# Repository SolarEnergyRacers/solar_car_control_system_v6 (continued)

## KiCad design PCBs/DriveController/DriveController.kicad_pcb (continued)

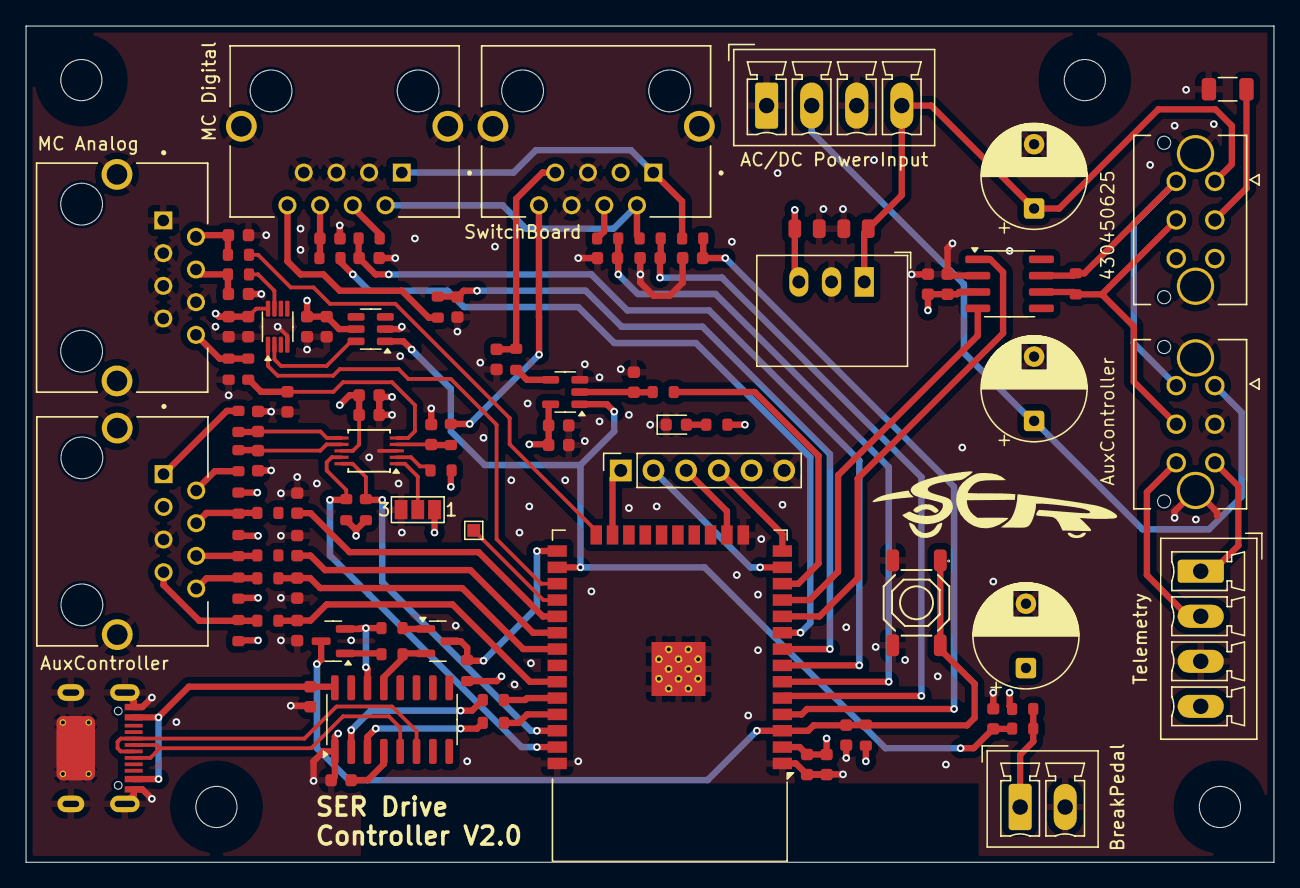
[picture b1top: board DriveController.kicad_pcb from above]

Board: 4 copper layers, 97.0 x 65.0 mm, 106 parts (0 on the bottom side), 75 nets.

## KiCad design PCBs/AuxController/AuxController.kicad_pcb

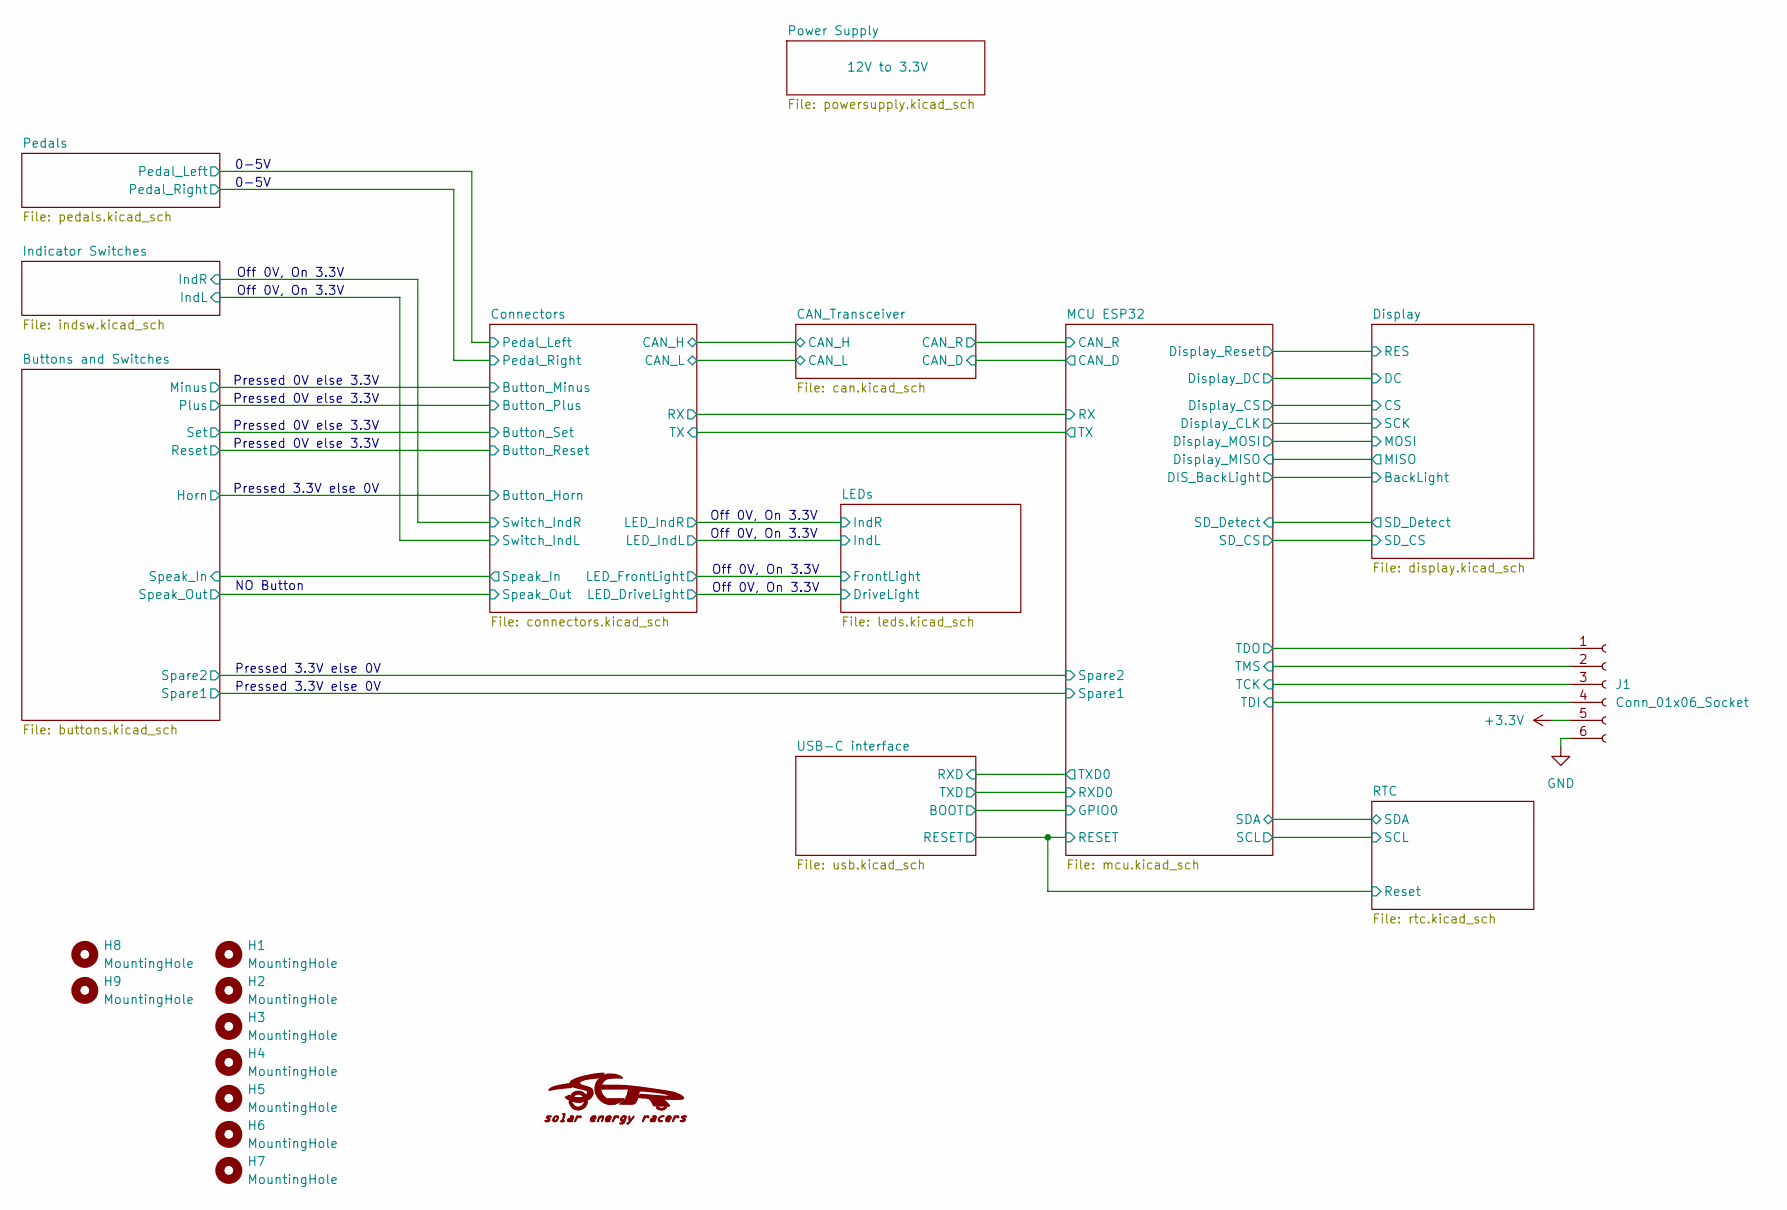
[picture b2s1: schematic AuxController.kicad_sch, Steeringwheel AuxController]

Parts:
G1: LOGO; SER_Logo
H1, H2, H3, H4, H5, H6, H7: MountingHole; MountingHole_3.2mm_M3_No_Copper
H8, H9: MountingHole; MountingHole_6.5mm_mod
J1: Conn_01x06_Socket; PinSocket_1x06_P2.54mm_Horizontal

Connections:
+3.3V: J1.5; also elsewhere on the board
/MCU ESP32/TCK: J1.3; also elsewhere on the board
/MCU ESP32/TDI: J1.4; also elsewhere on the board
/MCU ESP32/TDO: J1.1; also elsewhere on the board
/MCU ESP32/TMS: J1.2; also elsewhere on the board
GND: J1.6; also elsewhere on the board

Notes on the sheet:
Pressed 0V else 3.3V
0-5V
NO Button
Off 0V, On 3.3V
Pressed 3.3V else 0V

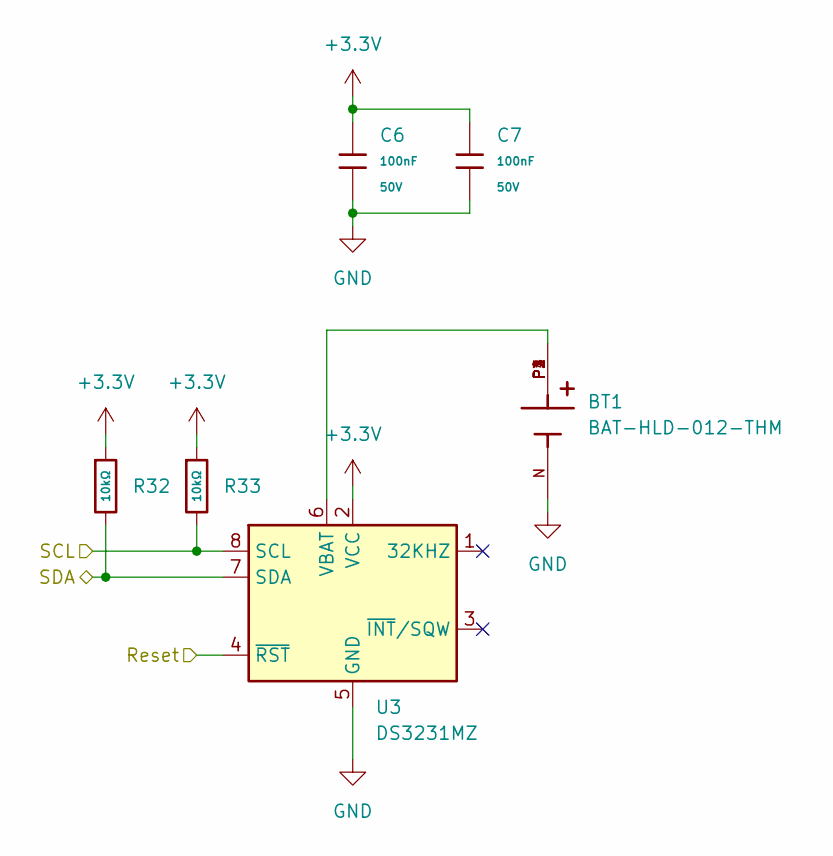
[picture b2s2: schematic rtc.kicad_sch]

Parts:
BT1: BAT-HLD-012-THM; BAT_BAT-HLD-012-THM
C6, C7: 100nF; C_0603; Voltage Rated 50V; Tolerance ±10%; Part CC0603KRX7R9BB104; LCSC C14663
R32, R33: 10kΩ; R_0603; Overload Voltage (Max) 75V; Tolerance ±1%; Part 0603WAF1002T5E; LCSC C25804
U3: DS3231MZ; SOIC-8_3.9x4.9mm_P1.27mm

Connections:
+3.3V: C6.1, C7.1, R32.1, R33.1, U3.2 (VCC); also elsewhere on the board
/MCU ESP32/RESET: U3.4 (~RST); also elsewhere on the board
/MCU ESP32/SCL: R33.2, U3.8 (SCL); also elsewhere on the board
/MCU ESP32/SDA: R32.2, U3.7 (SDA); also elsewhere on the board
GND: BT1.N, C6.2, C7.2, U3.5 (GND); also elsewhere on the board
unnamed: BT1.P1, BT1.P2, BT1.P3, BT1.P4, U3.6 (VBAT)

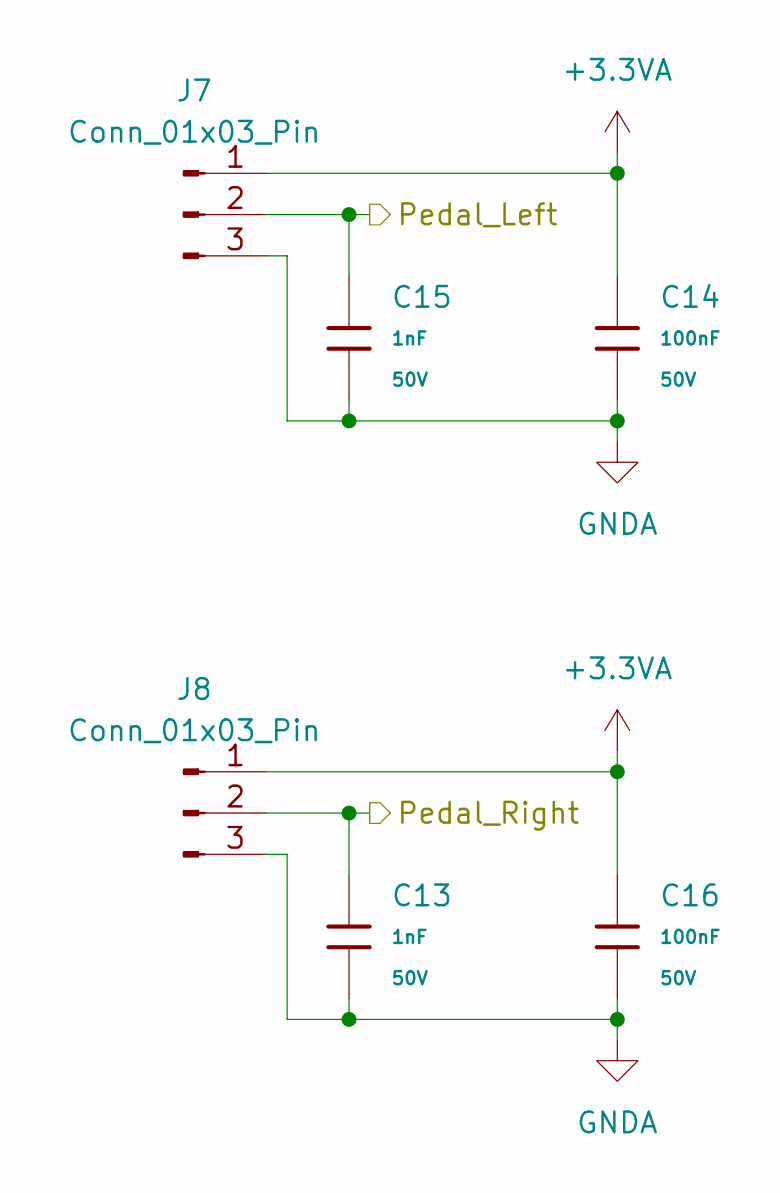
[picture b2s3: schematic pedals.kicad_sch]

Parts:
C13, C15: 1nF; C_0603; Voltage Rated 50V; Tolerance ±10%; Part CL10B102KB8NNNC; LCSC C1588
C14, C16: 100nF; C_0603; Voltage Rated 50V; Tolerance ±10%; Part CC0603KRX7R9BB104; LCSC C14663
J7, J8: Conn_01x03_Pin; PinHeader_1x03_P2.54mm_Vertical

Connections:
+3.3VA: C14.1, C16.1, J7.1, J8.1; also elsewhere on the board
/Connectors/Pedal_Left: C15.1, J7.2; also elsewhere on the board
/Connectors/Pedal_Right: C13.1, J8.2; also elsewhere on the board
GNDA: C13.2, C14.2, C15.2, C16.2, J7.3, J8.3; also elsewhere on the board

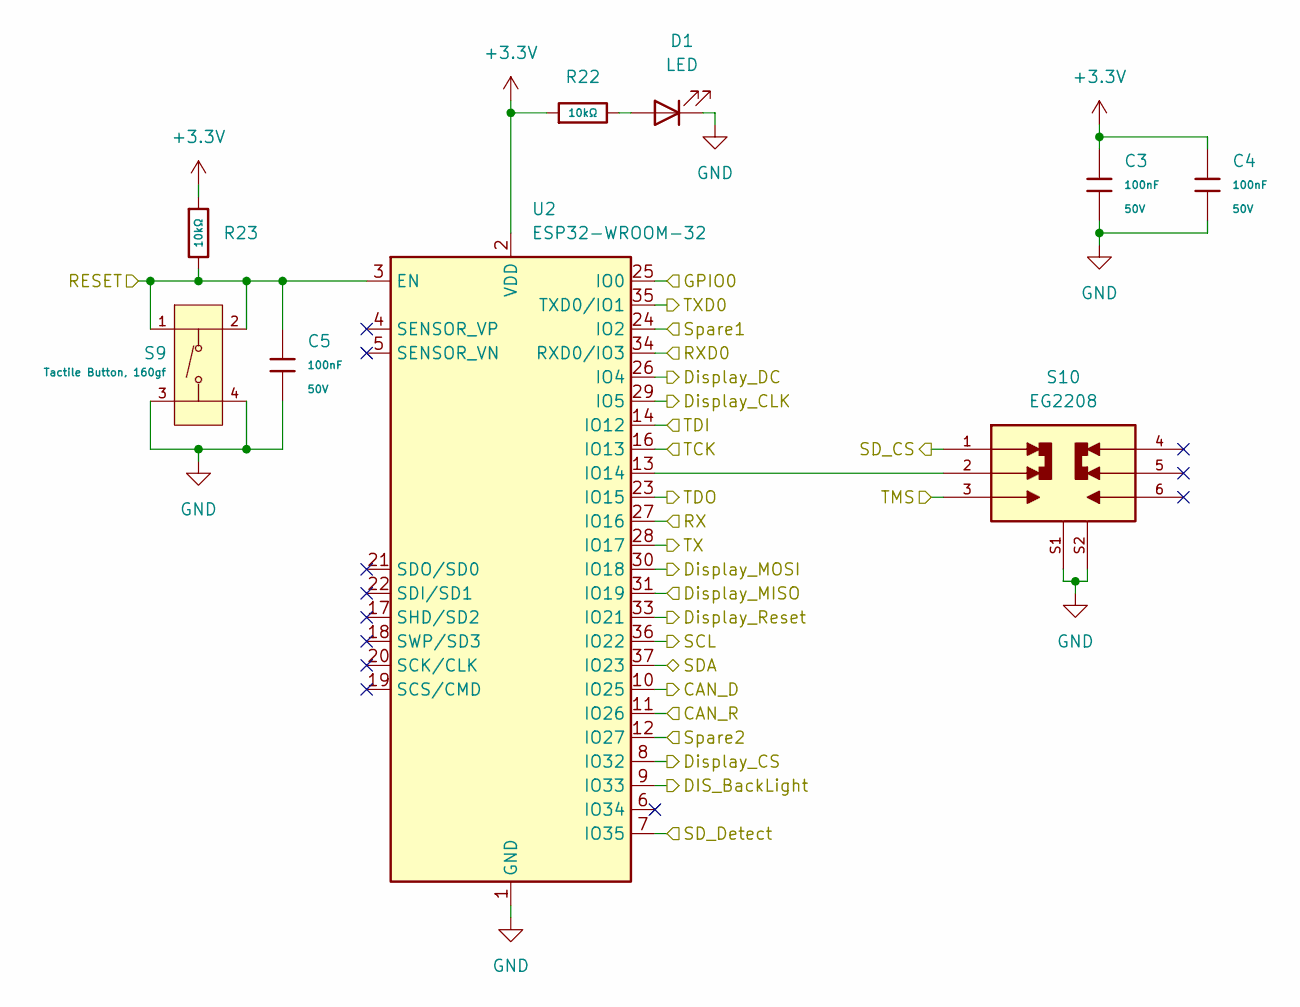
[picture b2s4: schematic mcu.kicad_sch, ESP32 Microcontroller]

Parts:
C3, C4, C5: 100nF; C_0603; Voltage Rated 50V; Tolerance ±10%; Part CC0603KRX7R9BB104; LCSC C14663
D1: LED; LED_0603_1608Metric
R22, R23: 10kΩ; R_0603; Overload Voltage (Max) 75V; Tolerance ±1%; Part 0603WAF1002T5E; LCSC C25804
S9: Tactile Button, 160gf; SW-SMD_4P-L5.1-W5.1-P3.70-LS6.5-TL-2; Voltage Rating (Dc) 12V; Part TS-1187A-B-A-B; LCSC C318884
S10: EG2208; SW_EG2208; PARTREV C
U2: ESP32-WROOM-32

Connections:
+3.3V: C3.1, C4.1, R22.1, R23.1, U2.2 (VDD); also elsewhere on the board
/Buttons and Switches/Spare1: U2.24 (IO2); also elsewhere on the board
/Buttons and Switches/Spare2: U2.12 (IO27); also elsewhere on the board
/CAN_Transceiver/CAN_D: U2.10 (IO25); also elsewhere on the board
/CAN_Transceiver/CAN_R: U2.11 (IO26); also elsewhere on the board
/Connectors/RX: U2.27 (IO16); also elsewhere on the board
/Connectors/TX: U2.28 (IO17); also elsewhere on the board
/Display/BackLight: U2.9 (IO33); also elsewhere on the board
/Display/CS: U2.8 (IO32); also elsewhere on the board
/Display/DC: U2.26 (IO4); also elsewhere on the board
/Display/MISO: U2.31 (IO19); also elsewhere on the board
/Display/MOSI: U2.30 (IO18); also elsewhere on the board
/Display/RES: U2.33 (IO21); also elsewhere on the board
/Display/SCK: U2.29 (IO5); also elsewhere on the board
/Display/SD_CS: S10.1; also elsewhere on the board
/Display/SD_Detect: U2.7 (IO35); also elsewhere on the board
/MCU ESP32/GPIO0: U2.25 (IO0); also elsewhere on the board
/MCU ESP32/RESET: C5.1, R23.2, S9.1 (A), S9.2 (B), U2.3 (EN); also elsewhere on the board
/MCU ESP32/RXD0: U2.34 (RXD0/IO3); also elsewhere on the board
/MCU ESP32/SCL: U2.36 (IO22); also elsewhere on the board
/MCU ESP32/SDA: U2.37 (IO23); also elsewhere on the board
/MCU ESP32/TCK: U2.16 (IO13); also elsewhere on the board
/MCU ESP32/TDI: U2.14 (IO12); also elsewhere on the board
/MCU ESP32/TDO: U2.23 (IO15); also elsewhere on the board
/MCU ESP32/TMS: S10.3; also elsewhere on the board
/MCU ESP32/TXD0: U2.35 (TXD0/IO1); also elsewhere on the board
GND: C3.2, C4.2, C5.2, D1.1 (K), S9.3 (C), S9.4 (D), S10.S1, S10.S2, U2.1 (GND), U2.15 (GND), U2.38 (GND), U2.39 (GND); also elsewhere on the board
unnamed: D1.2 (A), R22.2
unnamed: S10.2, U2.13 (IO14)

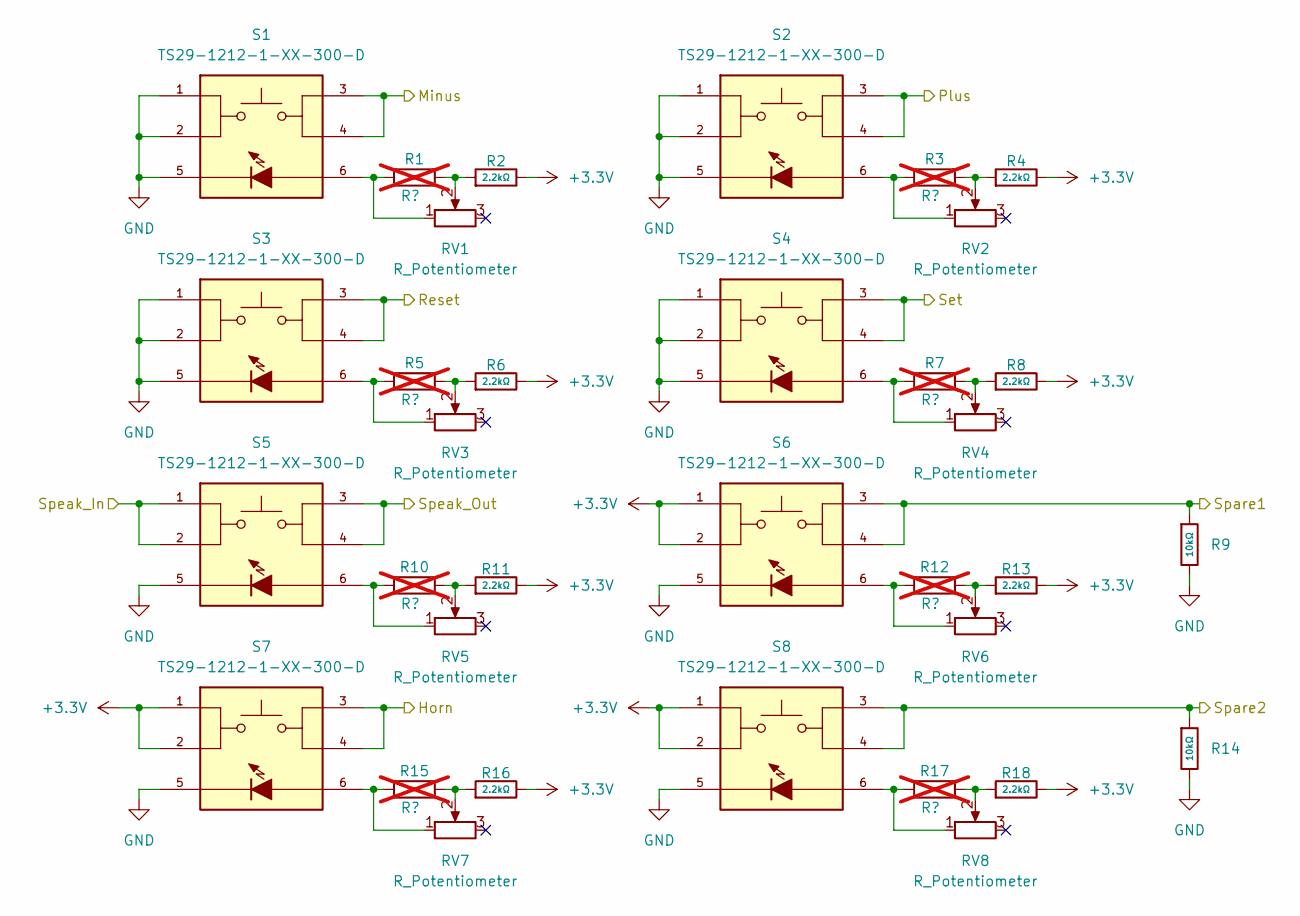
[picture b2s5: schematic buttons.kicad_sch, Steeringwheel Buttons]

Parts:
R1, R3, R5, R7, R10, R12, R15, R17: R?; R_0603_1608Metric; not fitted
R2, R4, R6, R8, R11, R13, R16, R18: 2.2kΩ; R_0603; Overload Voltage (Max) 75V; Tolerance ±1%; Part 0603WAF2201T5E; LCSC C4190
R9, R14: 10kΩ; R_0603; Overload Voltage (Max) 75V; Tolerance ±1%; Part 0603WAF1002T5E; LCSC C25804
RV1, RV2, RV3, RV4, RV5, RV6, RV7, RV8: R_Potentiometer; Potentiometer_Bourns_TC33X_Vertical
S1, S2, S3, S4, S5, S6, S7, S8: TS29-1212-1-XX-300-D; SW_TS29-1212-1-XX-300-D_mod; PARTREV 1.01

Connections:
+3.3V: R2.2, R4.2, R6.2, R8.2, R11.2, R13.2, R16.2, R18.2, S6.1, S6.2, S7.1, S7.2, S8.1, S8.2; also elsewhere on the board
/Buttons and Switches/Horn: S7.3, S7.4; also elsewhere on the board
/Buttons and Switches/Minus: S1.3, S1.4; also elsewhere on the board
/Buttons and Switches/Plus: S2.3, S2.4; also elsewhere on the board
/Buttons and Switches/Reset: S3.3, S3.4; also elsewhere on the board
/Buttons and Switches/Set: S4.3, S4.4; also elsewhere on the board
/Buttons and Switches/Spare1: R9.1, S6.3, S6.4; also elsewhere on the board
/Buttons and Switches/Spare2: R14.1, S8.3, S8.4; also elsewhere on the board
/Buttons and Switches/Speak_In: S5.1, S5.2; also elsewhere on the board
/Buttons and Switches/Speak_Out: S5.3, S5.4; also elsewhere on the board
GND: R9.2, R14.2, S1.1, S1.2, S1.5, S2.1, S2.2, S2.5, S3.1, S3.2, S3.5, S4.1, S4.2, S4.5, S5.5, S6.5, S7.5, S8.5; also elsewhere on the board
unnamed: R1.1, RV1.1, S1.6
unnamed: R1.2, R2.1, RV1.2
unnamed: R3.1, RV2.1, S2.6
unnamed: R3.2, R4.1, RV2.2
unnamed: R5.1, RV3.1, S3.6
unnamed: R5.2, R6.1, RV3.2
unnamed: R7.1, RV4.1, S4.6
unnamed: R7.2, R8.1, RV4.2
unnamed: R10.1, RV5.1, S5.6
unnamed: R10.2, R11.1, RV5.2
unnamed: R12.1, RV6.1, S6.6
unnamed: R12.2, R13.1, RV6.2
unnamed: R15.1, RV7.1, S7.6
unnamed: R15.2, R16.1, RV7.2
unnamed: R17.1, RV8.1, S8.6
unnamed: R17.2, R18.1, RV8.2

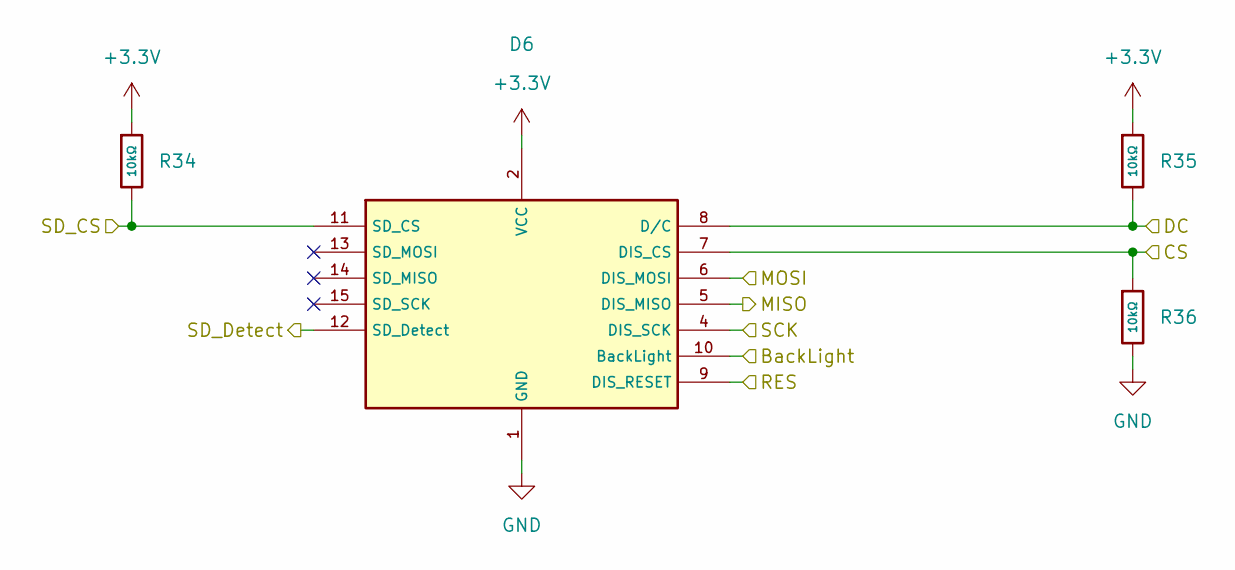
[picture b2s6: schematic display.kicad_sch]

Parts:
D6: ILI93_Display_Adafruit
R34, R35, R36: 10kΩ; R_0603; Overload Voltage (Max) 75V; Tolerance ±1%; Part 0603WAF1002T5E; LCSC C25804

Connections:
+3.3V: D6.2 (VCC), R34.1, R35.1; also elsewhere on the board
/Display/BackLight: D6.10 (BackLight); also elsewhere on the board
/Display/CS: D6.7 (DIS_CS), R36.1; also elsewhere on the board
/Display/DC: D6.8 (D/C), R35.2; also elsewhere on the board
/Display/MISO: D6.5 (DIS_MISO); also elsewhere on the board
/Display/MOSI: D6.6 (DIS_MOSI); also elsewhere on the board
/Display/RES: D6.9 (DIS_RESET); also elsewhere on the board
/Display/SCK: D6.4 (DIS_SCK); also elsewhere on the board
/Display/SD_CS: D6.11 (SD_CS), R34.2; also elsewhere on the board
/Display/SD_Detect: D6.12 (SD_Detect); also elsewhere on the board
GND: D6.1 (GND), R36.2; also elsewhere on the board

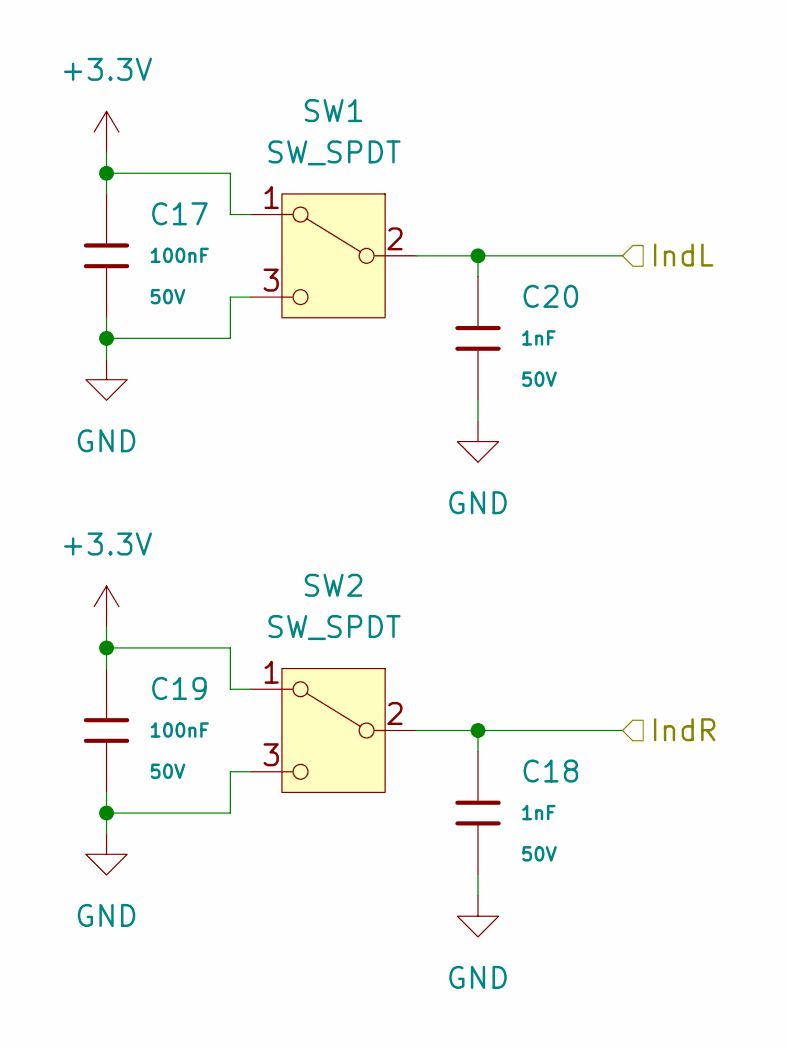
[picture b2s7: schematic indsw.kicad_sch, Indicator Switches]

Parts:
C17, C19: 100nF; C_0603; Voltage Rated 50V; Tolerance ±10%; Part CC0603KRX7R9BB104; LCSC C14663
C18, C20: 1nF; C_0603; Voltage Rated 50V; Tolerance ±10%; Part CL10B102KB8NNNC; LCSC C1588
SW1, SW2: SW_SPDT; PinHeader_1x03_P2.54mm_Vertical

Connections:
+3.3V: C17.1, C19.1, SW1.1 (A), SW2.1 (A); also elsewhere on the board
/Connectors/Switch_IndL: C20.1, SW1.2 (B); also elsewhere on the board
/Connectors/Switch_IndR: C18.1, SW2.2 (B); also elsewhere on the board
GND: C17.2, C18.2, C19.2, C20.2, SW1.3 (C), SW2.3 (C); also elsewhere on the board

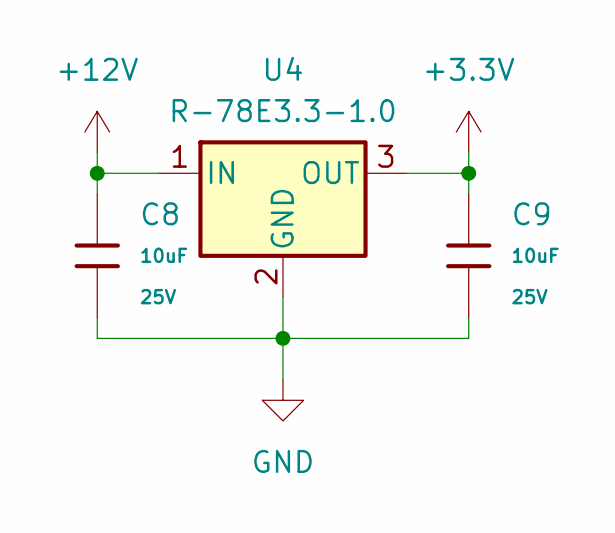
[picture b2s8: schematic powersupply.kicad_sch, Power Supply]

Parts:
C8, C9: 10uF; C_0805; Voltage Rated 25V; Tolerance ±10%; Part CL21A106KAYNNNE; LCSC C15850
U4: R-78E3.3-1.0; Converter_DCDC_RECOM_R-78E-0.5_THT

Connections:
+3.3V: C9.1, U4.3 (OUT); also elsewhere on the board
+12V: C8.1, U4.1 (IN); also elsewhere on the board
GND: C8.2, C9.2, U4.2 (GND); also elsewhere on the board

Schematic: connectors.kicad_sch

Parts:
J2: DriveController; CUI_CRJ027-1-TH; PARTREV 1.0
J3: 430450625; MOLEX_430450625; PARTREV H4
J4: Radio Enable; SAMESKY_SJ1-2503A; PARTREV 1.06
J5: ChassisBoard; CUI_CRJ027-1-TH; PARTREV 1.0
R19, R20, R42: R; R_0603_1608Metric; not fitted

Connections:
+3.3VA: J2.3; also elsewhere on the board
+12V: J3.1; also elsewhere on the board
/Buttons and Switches/Horn: J5.5; also elsewhere on the board
/Buttons and Switches/Minus: J2.8; also elsewhere on the board
/Buttons and Switches/Plus: J2.6; also elsewhere on the board
/Buttons and Switches/Reset: J2.7; also elsewhere on the board
/Buttons and Switches/Set: J2.4; also elsewhere on the board
/Buttons and Switches/Speak_In: J4.4; also elsewhere on the board
/Buttons and Switches/Speak_Out: J4.2, J4.3; also elsewhere on the board
/CAN_Transceiver/CAN_H: J3.4; also elsewhere on the board
/CAN_Transceiver/CAN_L: J3.5; also elsewhere on the board
/Connectors/LED_DriveLight: J5.8; also elsewhere on the board
/Connectors/LED_FrontLight: J5.7; also elsewhere on the board
/Connectors/LED_IndL: J5.4; also elsewhere on the board
/Connectors/LED_IndR: J5.1; also elsewhere on the board
/Connectors/Pedal_Left: J2.2; also elsewhere on the board
/Connectors/Pedal_Right: J2.1; also elsewhere on the board
/Connectors/RX: J3.3; also elsewhere on the board
/Connectors/Switch_IndL: J5.3; also elsewhere on the board
/Connectors/Switch_IndR: J5.2; also elsewhere on the board
/Connectors/TX: J3.6; also elsewhere on the board
GND: J3.2, J3.S1 (SHIELD1), J3.S2 (SHIELD2), J4.1, R19.1, R20.1, R42.1; also elsewhere on the board
GNDA: J2.5; also elsewhere on the board
unnamed: J2.S1 (SHIELD), R19.2
unnamed: J5.6, R42.2
unnamed: J5.S2 (SHIELD__1), R20.2

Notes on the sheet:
Modify Radio
No Ground Loop
Supply for Pedals

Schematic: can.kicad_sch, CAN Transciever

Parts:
C1, C2: 100nF; C_0603; Voltage Rated 50V; Tolerance ±10%; Part CC0603KRX7R9BB104; LCSC C14663
R21: 120Ω; R_0603; Overload Voltage (Max) 75V; Tolerance ±1%; Part 0603WAF1200T5E; LCSC C22787
U1: SN65HVD232; SOIC-8_3.9x4.9mm_P1.27mm

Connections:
+3.3V: C1.1, C2.1, U1.3 (VCC); also elsewhere on the board
/CAN_Transceiver/CAN_D: U1.1 (D); also elsewhere on the board
/CAN_Transceiver/CAN_H: R21.1, U1.7 (CANH); also elsewhere on the board
/CAN_Transceiver/CAN_L: R21.2, U1.6 (CANL); also elsewhere on the board
/CAN_Transceiver/CAN_R: U1.4 (R); also elsewhere on the board
GND: C1.2, C2.2, U1.2 (GND); also elsewhere on the board

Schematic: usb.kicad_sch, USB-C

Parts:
C10, C11: 100nF; C_0603; Voltage Rated 50V; Tolerance ±10%; Part CC0603KRX7R9BB104; LCSC C14663
C12: 1uF; C_0603; Voltage Rated 50V; Tolerance ±10%; Part CL10A105KB8NNNC; LCSC C15849
J6: Connector, USB-TYPE-C-16P; TYPE-C-SMD_HX-TYPE-C-16PIN; LCSC C2927039
Q1, Q2: MMBT5551L; SOT-23
R37, R38: 470Ω; R_0603; Overload Voltage (Max) 75V; Tolerance ±1%; Part 0603WAF4700T5E; LCSC C23179
R39, R40, R41: 10kΩ; R_0603; Overload Voltage (Max) 75V; Tolerance ±1%; Part 0603WAF1002T5E; LCSC C25804
U5: CH340C; SOIC-16_3.9x9.9mm_P1.27mm

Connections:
+3.3V: R41.1; also elsewhere on the board
/MCU ESP32/GPIO0: Q2.3 (C), R41.2; also elsewhere on the board
/MCU ESP32/RESET: C12.1, Q1.3 (C); also elsewhere on the board
/MCU ESP32/RXD0: R37.2; also elsewhere on the board
/MCU ESP32/TXD0: R38.2; also elsewhere on the board
DTR: Q2.2 (E), R39.1, U5.13 (~DTR)
GND: C10.2, C11.1, C12.2, J6.A12B1 (GND), J6.B12A1 (GND), J6.S1 (SHIELD), U5.1 (GND); also elsewhere on the board
unnamed: Q1.1 (B), R39.2
unnamed: Q2.1 (B), R40.2
unnamed: R38.1, U5.3 (RXD)
unnamed: R37.1, U5.2 (TXD)
unnamed: J6.A6 (D+), J6.B6 (D+), U5.5 (UD+)
unnamed: J6.A7 (D-), J6.B7 (D-), U5.6 (UD-)
unnamed: C10.1, U5.4 (V3)
unnamed: C11.2, J6.A9B4 (VBUS), J6.B9A4 (VBUS), U5.16 (VCC)
RTS: Q1.2 (E), R40.1, U5.14 (~RTS)

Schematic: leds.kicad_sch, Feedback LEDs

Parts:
D2: INDL; LED_D3.0mm
D3: DRIVELIGHT; LED_D3.0mm
D4: FRONTLIGHT; LED_D3.0mm
D5: INDR; LED_D3.0mm
R24, R25, R26, R27: 2.2kΩ; R_0603; Overload Voltage (Max) 75V; Tolerance ±1%; Part 0603WAF2201T5E; LCSC C4190
R28, R29, R30, R31: R?; R_0603_1608Metric; not fitted
RV9, RV10, RV11, RV12: R_Potentiometer; Potentiometer_Bourns_TC33X_Vertical

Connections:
/Connectors/LED_DriveLight: R25.2; also elsewhere on the board
/Connectors/LED_FrontLight: R26.2; also elsewhere on the board
/Connectors/LED_IndL: R24.2; also elsewhere on the board
/Connectors/LED_IndR: R27.2; also elsewhere on the board
GND: D2.1 (K), D3.1 (K), D4.1 (K), D5.1 (K); also elsewhere on the board
unnamed: D2.2 (A), R28.1, RV9.1
unnamed: D3.2 (A), R29.1, RV10.1
unnamed: D4.2 (A), R30.1, RV11.1
unnamed: D5.2 (A), R31.1, RV12.1
unnamed: R24.1, R28.2, RV9.2
unnamed: R25.1, R29.2, RV10.2
unnamed: R26.1, R30.2, RV11.2
unnamed: R27.1, R31.2, RV12.2

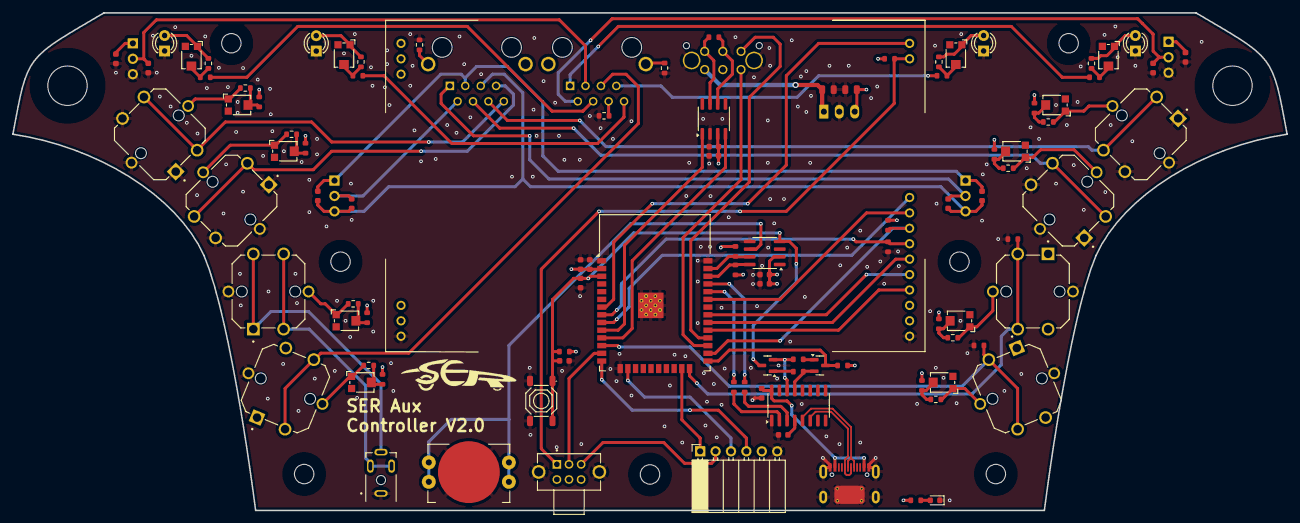
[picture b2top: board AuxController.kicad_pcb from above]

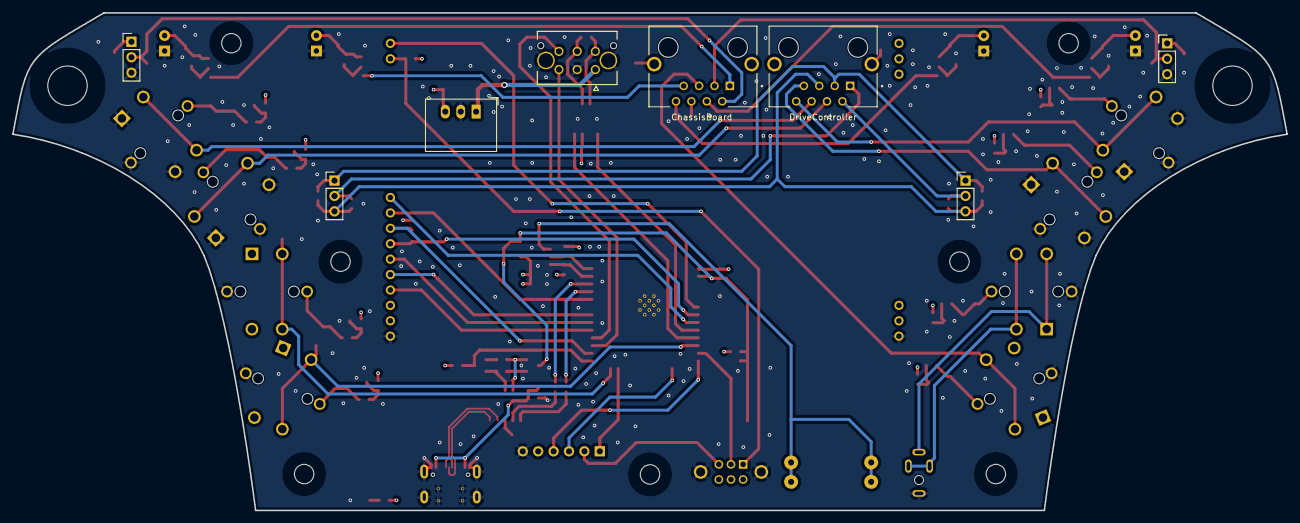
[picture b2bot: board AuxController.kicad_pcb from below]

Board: 4 copper layers, 210.0 x 82.0 mm, 118 parts (8 on the bottom side), 87 nets.

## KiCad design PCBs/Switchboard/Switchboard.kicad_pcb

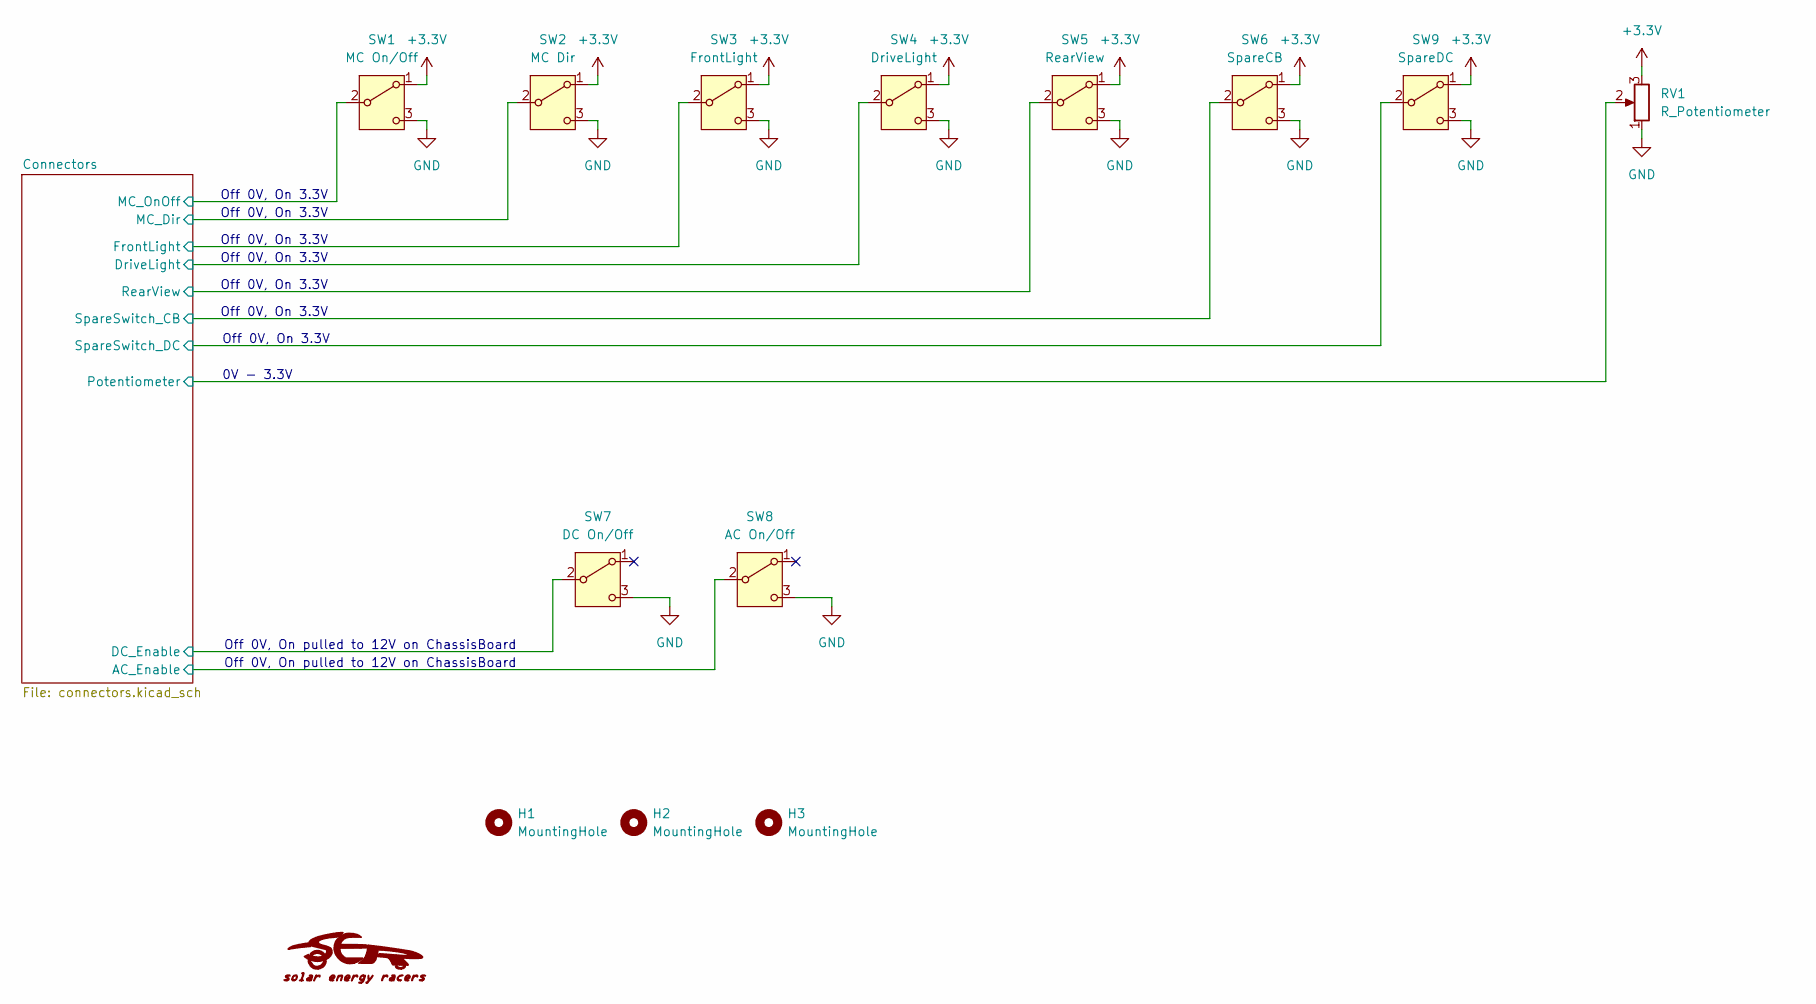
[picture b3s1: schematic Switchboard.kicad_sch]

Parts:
G1: LOGO; SER_Logo
H1, H2, H3: MountingHole; MountingHole_3.2mm_M3_No_Copper
RV1: R_Potentiometer; P0915N-EC15BR10K_BIT
SW1: MC On/Off; SW_100SP1T1B1M2QEH
SW2: MC Dir; SW_100SP1T1B1M2QEH
SW3: FrontLight; SW_100SP1T1B1M2QEH
SW4: DriveLight; SW_100SP1T1B1M2QEH
SW5: RearView; SW_100SP1T1B1M2QEH
SW6: SpareCB; SW_100SP1T1B1M2QEH
SW7: DC On/Off; SW_100SP1T1B1M2QEH
SW8: AC On/Off; SW_100SP1T1B1M2QEH
SW9: SpareDC; SW_100SP1T1B1M2QEH

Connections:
+3.3V: RV1.3, SW1.1 (A), SW2.1 (A), SW3.1 (A), SW4.1 (A), SW5.1 (A), SW6.1 (A), SW9.1 (A); also elsewhere on the board
/Connectors/AC_Enable: SW8.2 (B); also elsewhere on the board
/Connectors/DC_Enable: SW7.2 (B); also elsewhere on the board
/Connectors/DriveLight: SW4.2 (B); also elsewhere on the board
/Connectors/FrontLight: SW3.2 (B); also elsewhere on the board
/Connectors/MC_Dir: SW2.2 (B); also elsewhere on the board
/Connectors/MC_OnOff: SW1.2 (B); also elsewhere on the board
/Connectors/Potentiometer: RV1.2; also elsewhere on the board
/Connectors/RearView: SW5.2 (B); also elsewhere on the board
/Connectors/SpareSwitch_CB: SW6.2 (B); also elsewhere on the board
/Connectors/SpareSwitch_DC: SW9.2 (B); also elsewhere on the board
GND: RV1.1, SW1.3 (C), SW2.3 (C), SW3.3 (C), SW4.3 (C), SW5.3 (C), SW6.3 (C), SW7.3 (C), SW8.3 (C), SW9.3 (C); also elsewhere on the board

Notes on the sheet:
Off 0V, On 3.3V
Off 0V, On pulled to 12V on ChassisBoard
0V - 3.3V

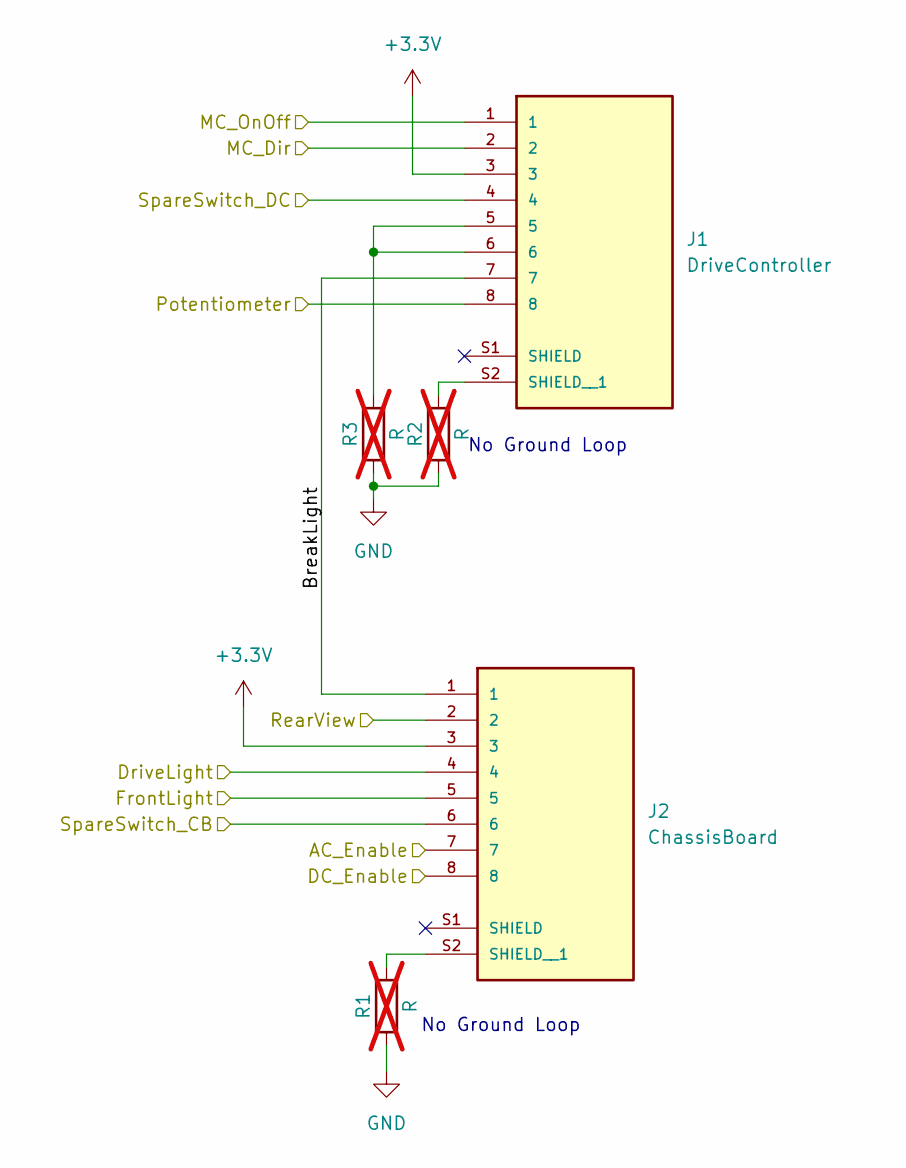
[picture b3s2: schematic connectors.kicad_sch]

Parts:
J1: DriveController; CUI_CRJ027-1-TH; PARTREV 1.0
J2: ChassisBoard; CUI_CRJ027-1-TH; PARTREV 1.0
R1, R2, R3: R; R_0603_1608Metric; not fitted

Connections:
+3.3V: J1.3, J2.3; also elsewhere on the board
/Connectors/AC_Enable: J2.7; also elsewhere on the board
/Connectors/BreakLight: J1.7, J2.1
/Connectors/DC_Enable: J2.8; also elsewhere on the board
/Connectors/DriveLight: J2.4; also elsewhere on the board
/Connectors/FrontLight: J2.5; also elsewhere on the board
/Connectors/MC_Dir: J1.2; also elsewhere on the board
/Connectors/MC_OnOff: J1.1; also elsewhere on the board
/Connectors/Potentiometer: J1.8; also elsewhere on the board
/Connectors/RearView: J2.2; also elsewhere on the board
/Connectors/SpareSwitch_CB: J2.6; also elsewhere on the board
/Connectors/SpareSwitch_DC: J1.4; also elsewhere on the board
GND: R1.1, R2.1, R3.1; also elsewhere on the board
unnamed: J1.5, J1.6, R3.2
unnamed: J1.S2 (SHIELD__1), R2.2
unnamed: J2.S2 (SHIELD__1), R1.2

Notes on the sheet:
No Ground Loop
